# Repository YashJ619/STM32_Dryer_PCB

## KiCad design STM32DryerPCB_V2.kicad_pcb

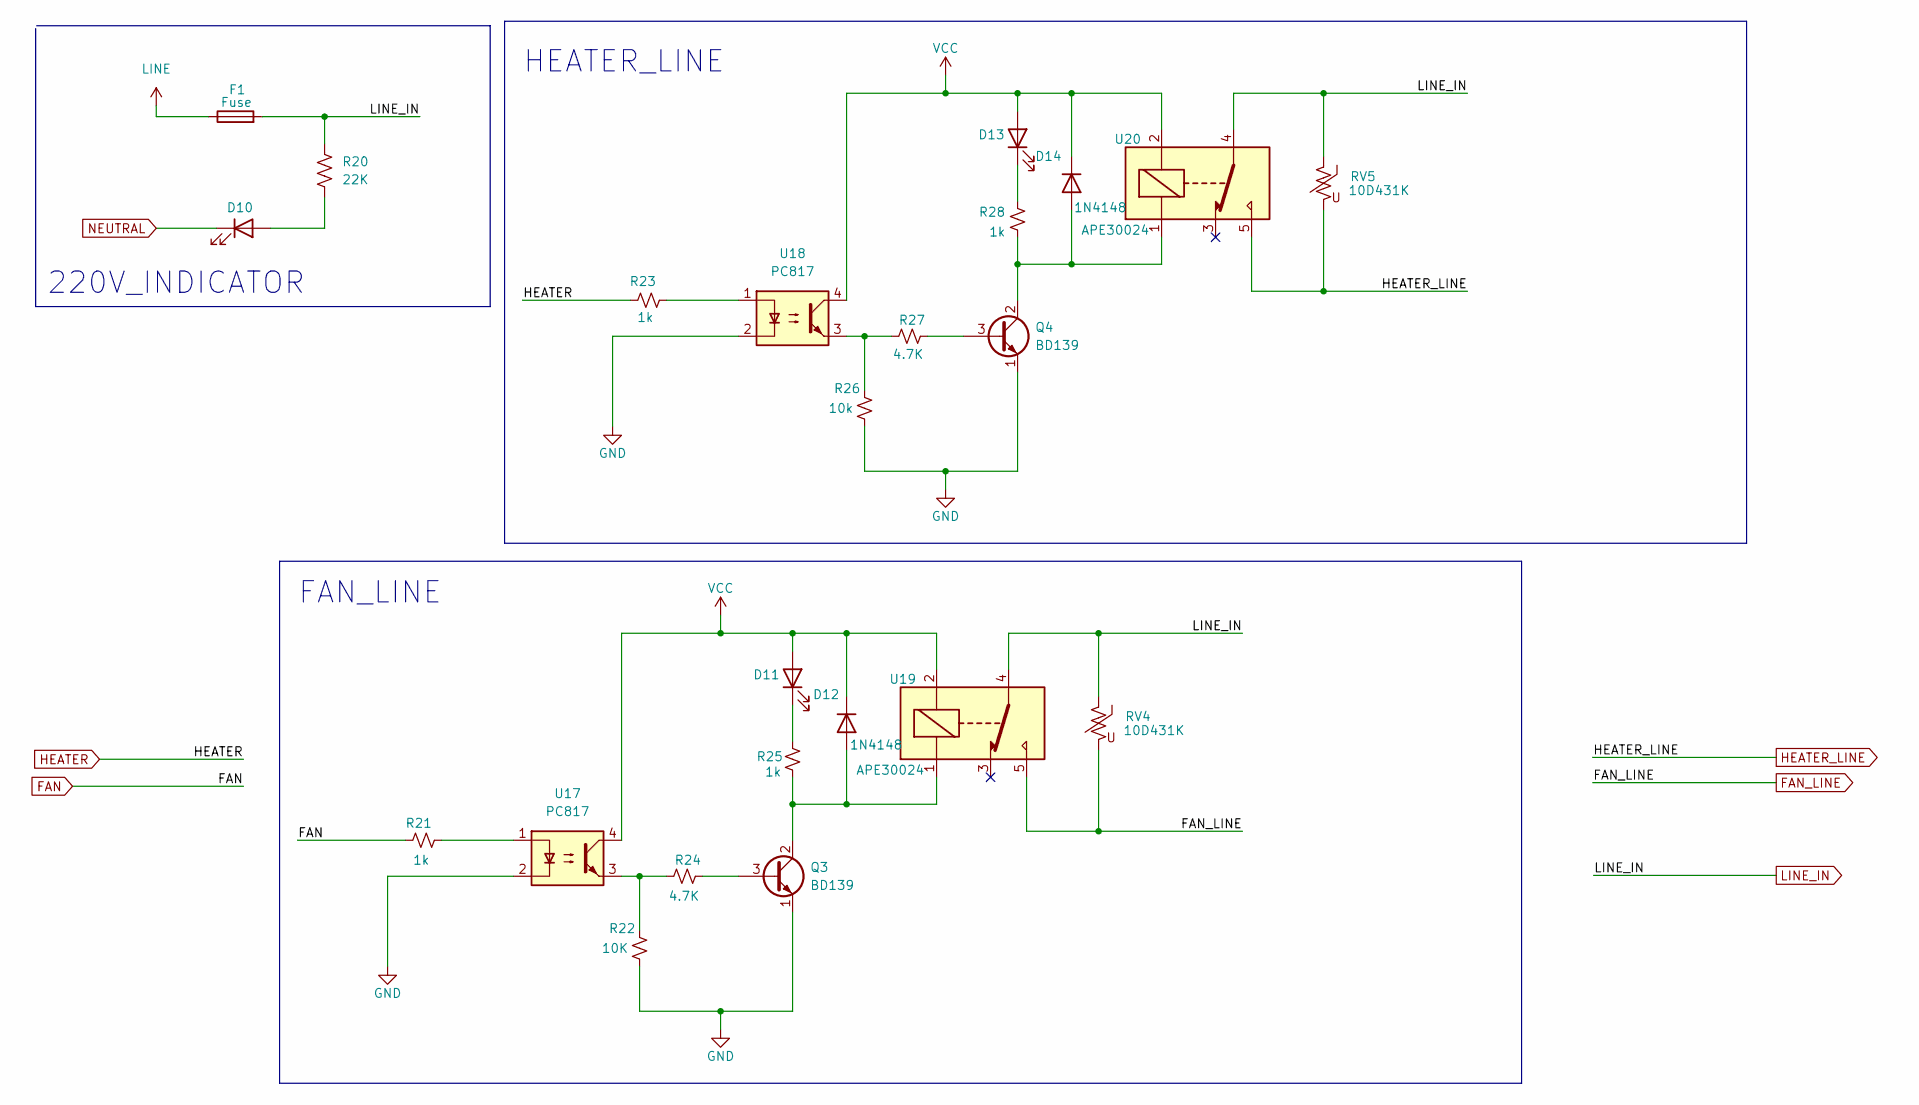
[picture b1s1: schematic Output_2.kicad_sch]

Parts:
D10, D11, D13: LED; LED_D3.0mm
D12, D14: 1N4148; D_DO-41_SOD81_P10.16mm_Horizontal
F1: Fuse; Fuseholder_Clip-5x20mm_Keystone_3518P_Inline_P23.11x6.76mm_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
Q3, Q4: BD139; TO-126-3_Vertical
R20: 22K; R_Axial_DIN0207_L6.3mm_D2.5mm_P10.16mm_Horizontal
R21, R23, R25, R28: 1k; R_Axial_DIN0207_L6.3mm_D2.5mm_P10.16mm_Horizontal
R22: 10K; R_Axial_DIN0207_L6.3mm_D2.5mm_P10.16mm_Horizontal
R24, R27: 4.7K; R_Axial_DIN0207_L6.3mm_D2.5mm_P10.16mm_Horizontal
R26: 10k; R_Axial_DIN0207_L6.3mm_D2.5mm_P10.16mm_Horizontal
RV4, RV5: 10D431K; RV_Disc_D7mm_W5.7mm_P5mm
U17, U18: PC817; DIP-4_W7.62mm_LongPads
U19, U20: APE30024; Relay_SPDT_28L_5W

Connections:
FAN: R21.1; also elsewhere on the board
FAN_LINE: RV4.2, U19.5; also elsewhere on the board
GND: Q3.1 (E), Q4.1 (E), R22.1, R26.1, U17.2, U18.2; also elsewhere on the board
HEATER: R23.1; also elsewhere on the board
HEATER_LINE: RV5.2, U20.5; also elsewhere on the board
LINE: F1.1; also elsewhere on the board
LINE_IN: F1.2, R20.1, RV4.1, RV5.1, U19.4, U20.4; also elsewhere on the board
NEUTRAL: D10.1 (K); also elsewhere on the board
unnamed: D10.2 (A), R20.2
unnamed: D11.1 (K), R25.2
unnamed: D12.2 (A), Q3.2 (C), R25.1, U19.1
unnamed: D13.1 (K), R28.2
unnamed: D14.2 (A), Q4.2 (C), R28.1, U20.1
unnamed: Q3.3 (B), R24.2
unnamed: Q4.3 (B), R27.2
unnamed: R21.2, U17.1
unnamed: R22.2, R24.1, U17.3
unnamed: R23.2, U18.1
unnamed: R26.2, R27.1, U18.3
VCC: D11.2 (A), D12.1 (K), D13.2 (A), D14.1 (K), U17.4, U18.4, U19.2, U20.2; also elsewhere on the board

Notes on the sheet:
HEATER_LINE
FAN_LINE
220V_INDICATOR

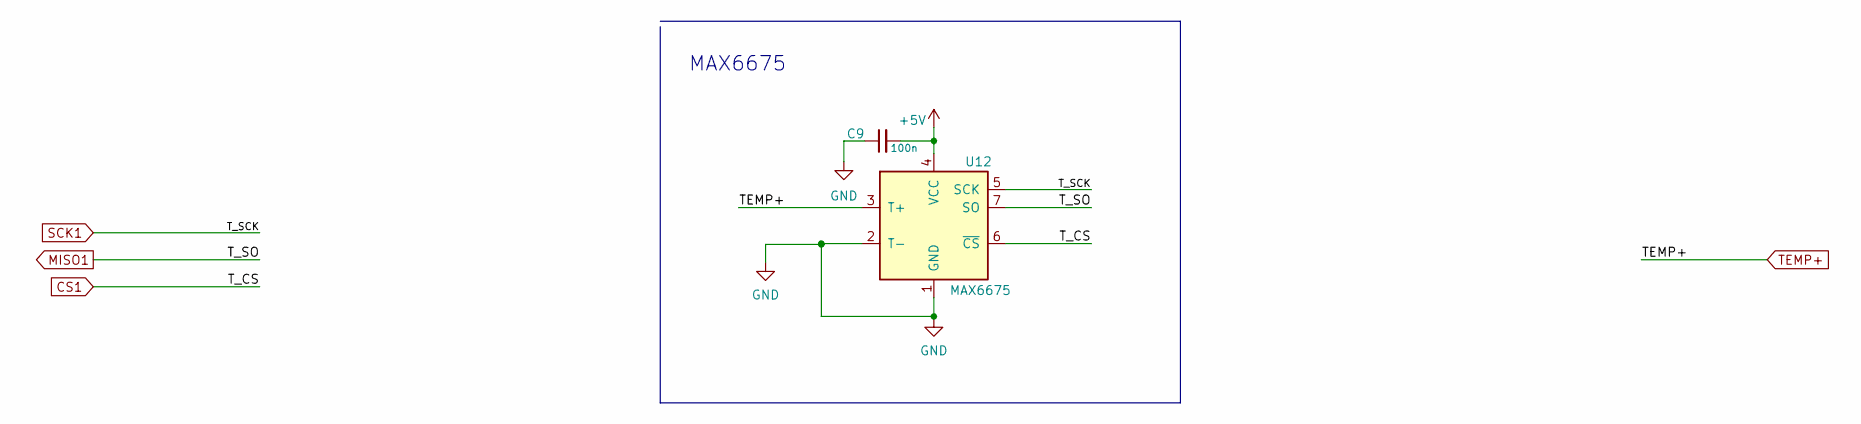
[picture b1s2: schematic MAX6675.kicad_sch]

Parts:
C9: 100n; C_Disc_D4.3mm_W1.9mm_P5.00mm
U12: MAX6675; SOIC-8_3.9x4.9mm_P1.27mm

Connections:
+5V: C9.2, U12.4 (VCC); also elsewhere on the board
CS1: U12.6 (~CS); also elsewhere on the board
GND: C9.1, U12.1 (GND), U12.2 (T-); also elsewhere on the board
MISO1: U12.7 (SO); also elsewhere on the board
SCK1: U12.5 (SCK); also elsewhere on the board
TEMP+: U12.3 (T+); also elsewhere on the board

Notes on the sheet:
MAX6675

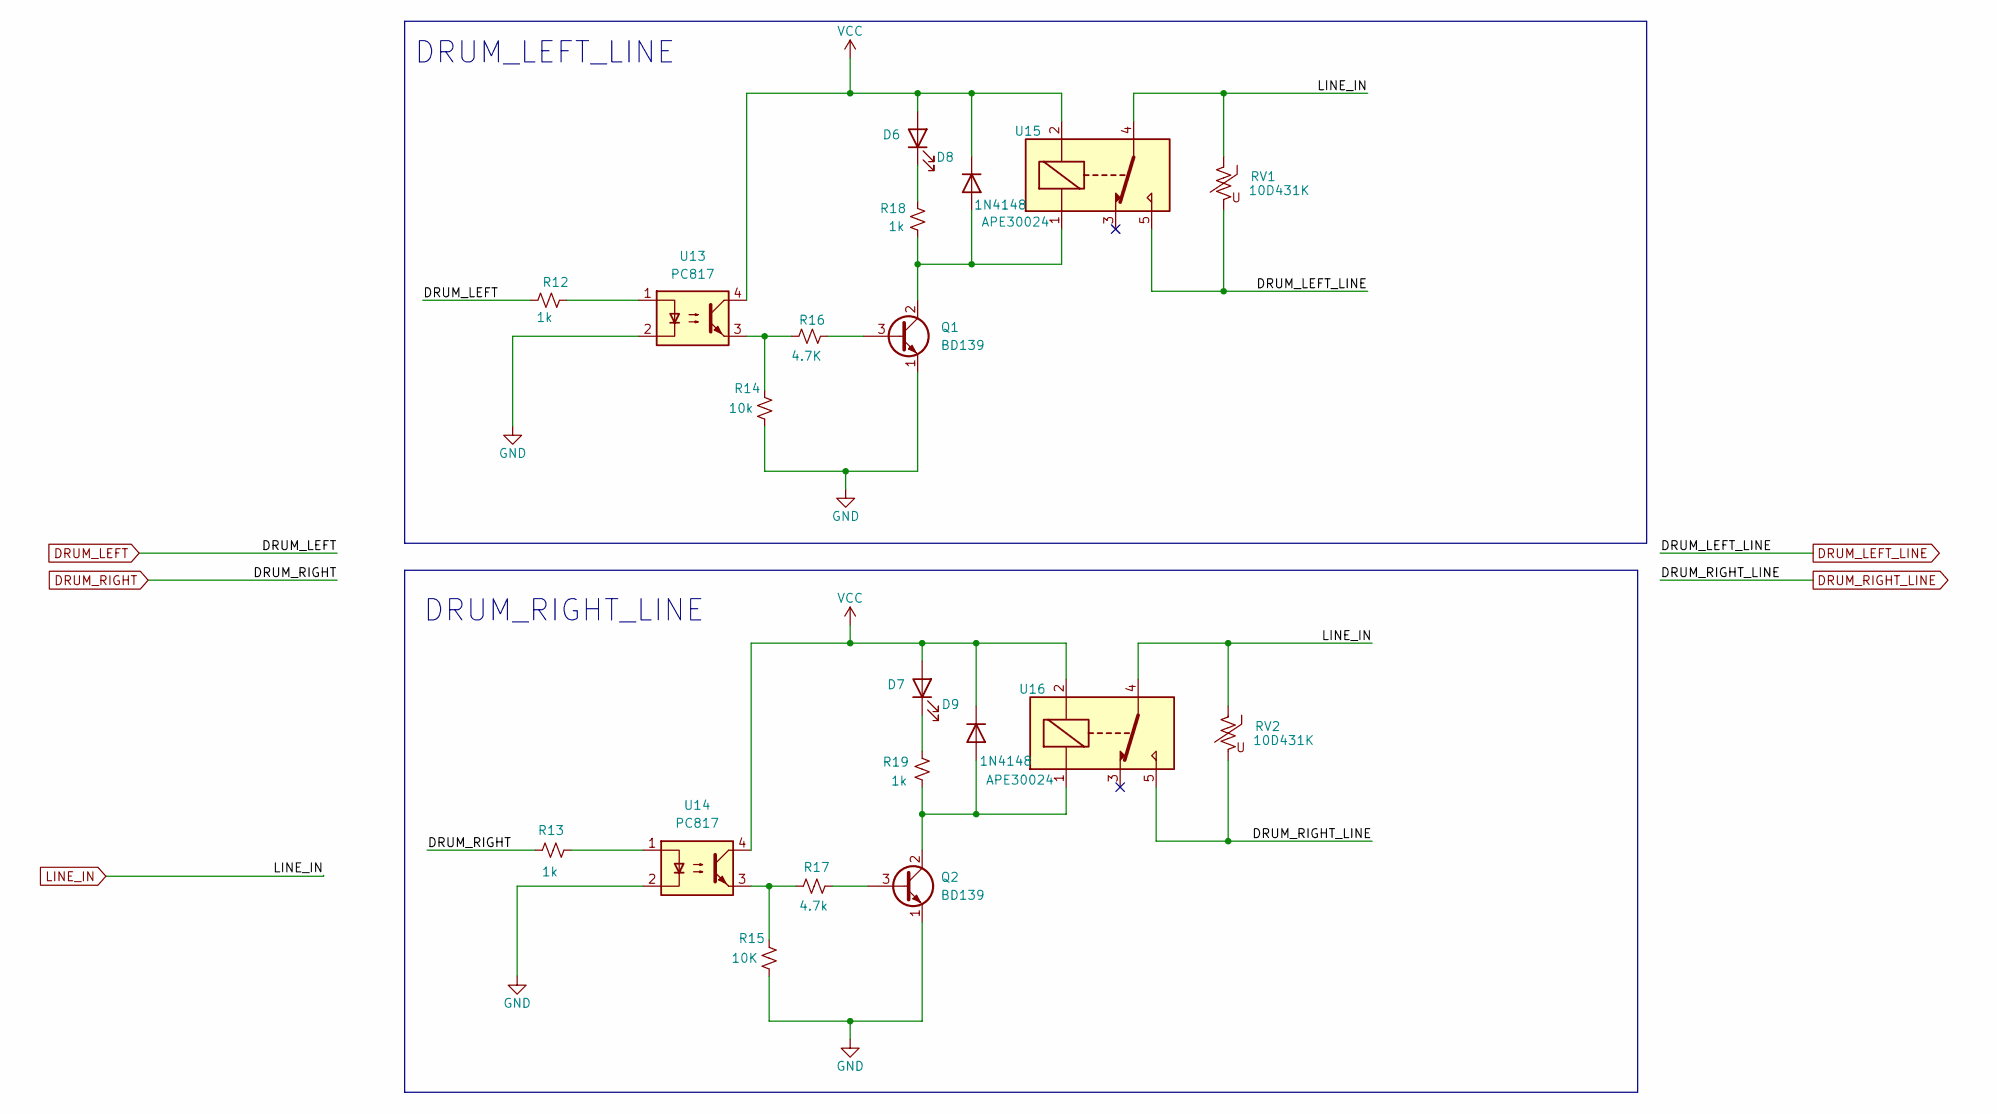
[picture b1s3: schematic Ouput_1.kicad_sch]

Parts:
D6, D7: LED; LED_D3.0mm
D8, D9: 1N4148; D_DO-41_SOD81_P10.16mm_Horizontal
Q1, Q2: BD139; TO-126-3_Vertical
R12, R13, R18, R19: 1k; R_Axial_DIN0207_L6.3mm_D2.5mm_P10.16mm_Horizontal
R14: 10k; R_Axial_DIN0207_L6.3mm_D2.5mm_P10.16mm_Horizontal
R15: 10K; R_Axial_DIN0207_L6.3mm_D2.5mm_P10.16mm_Horizontal
R16: 4.7K; R_Axial_DIN0207_L6.3mm_D2.5mm_P10.16mm_Horizontal
R17: 4.7k; R_Axial_DIN0207_L6.3mm_D2.5mm_P10.16mm_Horizontal
RV1, RV2: 10D431K; RV_Disc_D7mm_W5.7mm_P5mm
U13, U14: PC817; DIP-4_W7.62mm_LongPads
U15, U16: APE30024; Relay_SPDT_28L_5W

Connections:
DRUM_LEFT: R12.1; also elsewhere on the board
DRUM_LEFT_LINE: RV1.2, U15.5; also elsewhere on the board
DRUM_RIGHT: R13.1; also elsewhere on the board
DRUM_RIGHT_LINE: RV2.2, U16.5; also elsewhere on the board
GND: Q1.1 (E), Q2.1 (E), R14.1, R15.1, U13.2, U14.2; also elsewhere on the board
LINE_IN: RV1.1, RV2.1, U15.4, U16.4; also elsewhere on the board
unnamed: D6.1 (K), R18.2
unnamed: D7.1 (K), R19.2
unnamed: D8.2 (A), Q1.2 (C), R18.1, U15.1
unnamed: D9.2 (A), Q2.2 (C), R19.1, U16.1
unnamed: Q1.3 (B), R16.2
unnamed: Q2.3 (B), R17.2
unnamed: R12.2, U13.1
unnamed: R13.2, U14.1
unnamed: R14.2, R16.1, U13.3
unnamed: R15.2, R17.1, U14.3
VCC: D6.2 (A), D7.2 (A), D8.1 (K), D9.1 (K), U13.4, U14.4, U15.2, U16.2; also elsewhere on the board

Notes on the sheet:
DRUM_RIGHT_LINE
DRUM_LEFT_LINE

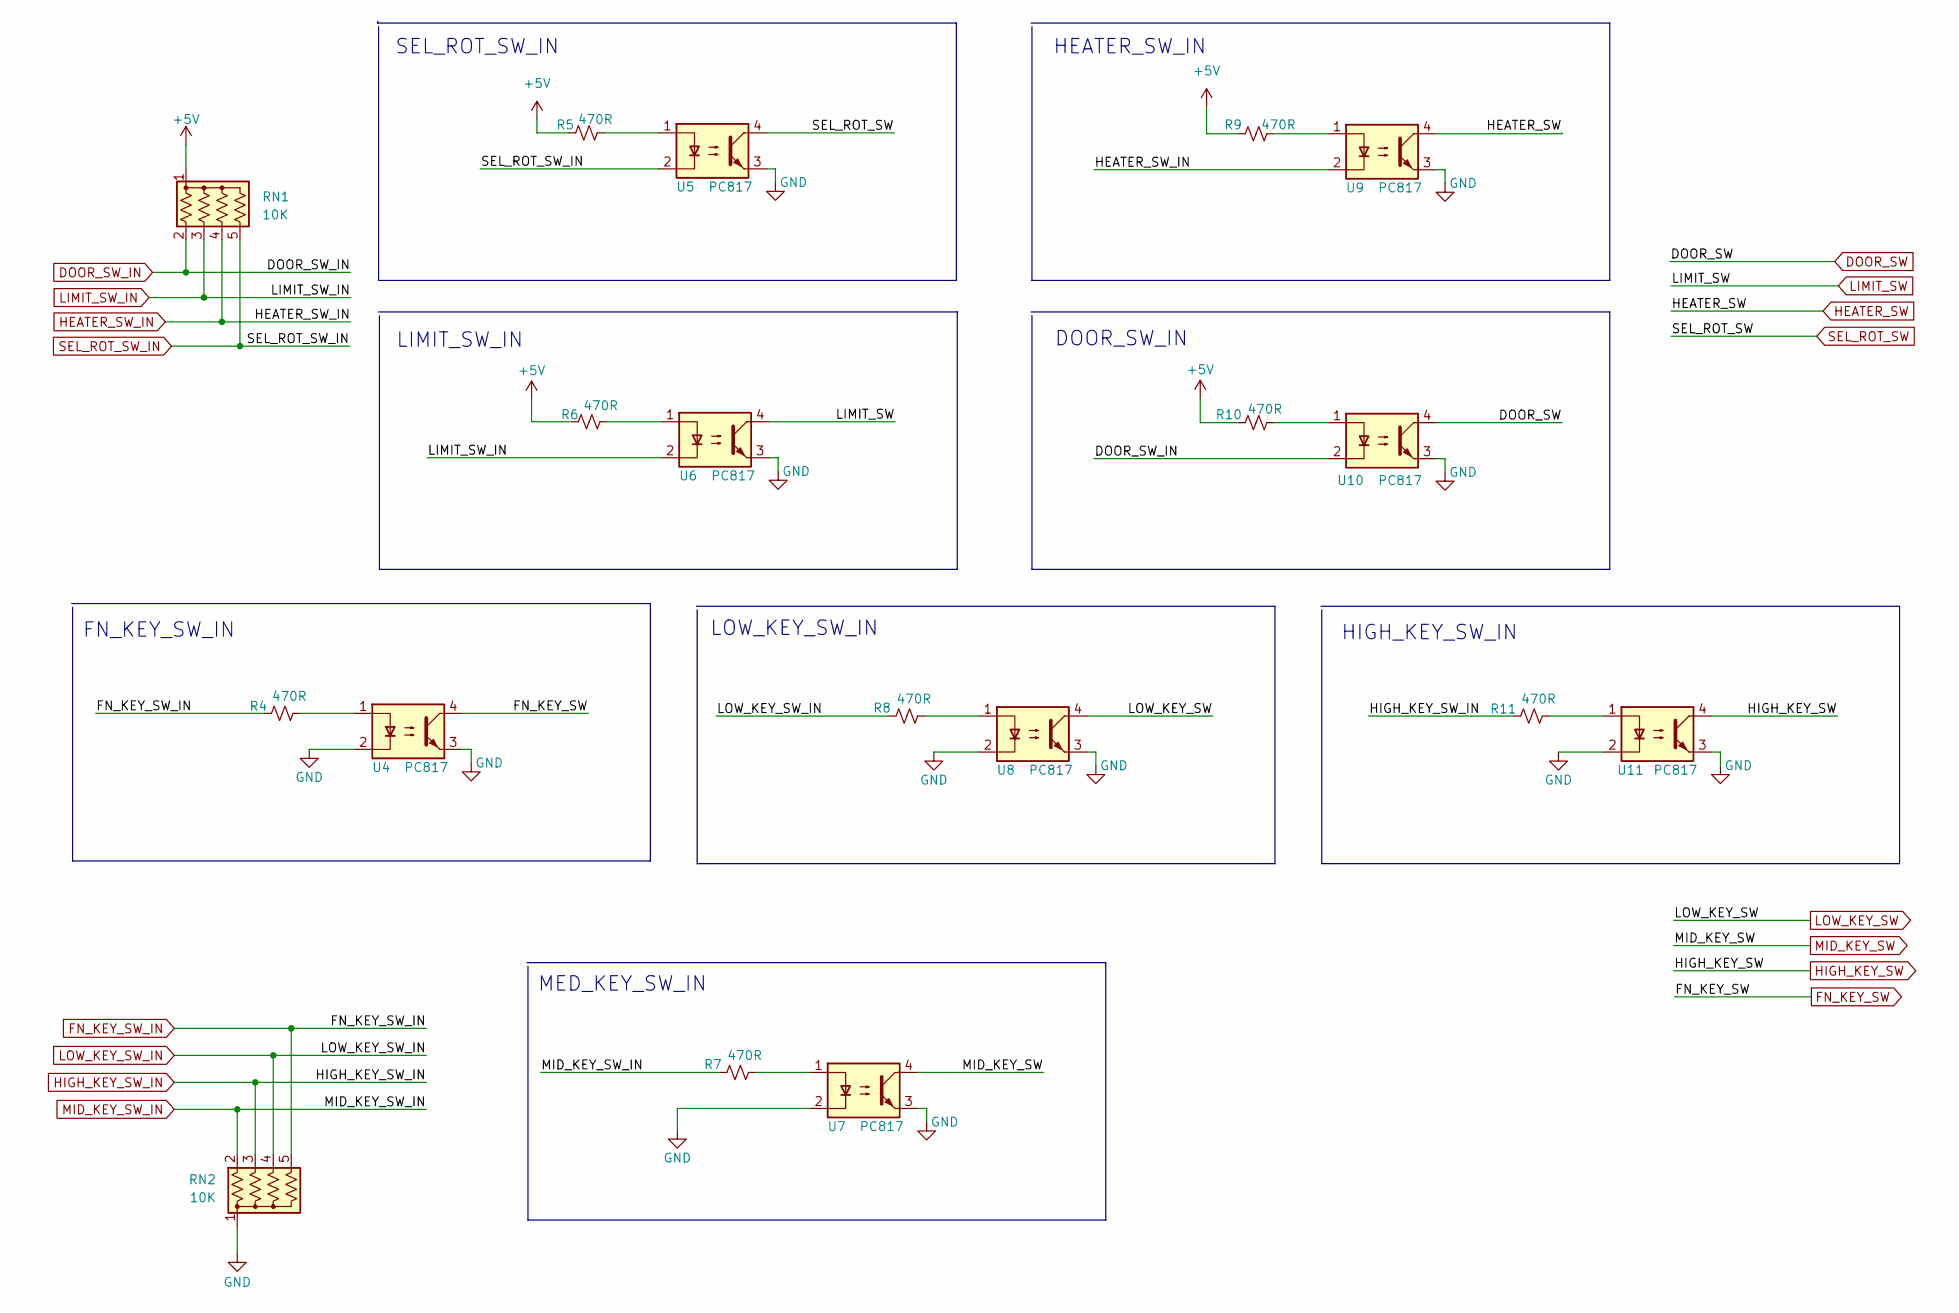
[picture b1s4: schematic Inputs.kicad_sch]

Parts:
R4, R5, R6, R7, R8, R9, R10, R11: 470R; R_Axial_DIN0207_L6.3mm_D2.5mm_P10.16mm_Horizontal
RN1, RN2: 10K; R_Array_SIP5
U4, U5, U6, U7, U8, U9, U10, U11: PC817; DIP-4_W7.62mm_LongPads

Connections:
+5V: R5.1, R6.1, R9.1, R10.1, RN1.1 (common); also elsewhere on the board
DOOR_SW: U10.4; also elsewhere on the board
DOOR_SW_IN: RN1.2 (R1), U10.2; also elsewhere on the board
FN_KEY_SW: U4.4; also elsewhere on the board
FN_KEY_SW_IN: R4.1, RN2.5 (R4); also elsewhere on the board
GND: RN2.1 (common), U4.2, U4.3, U5.3, U6.3, U7.2, U7.3, U8.2, U8.3, U9.3, U10.3, U11.2, U11.3; also elsewhere on the board
HEATER_SW: U9.4; also elsewhere on the board
HEATER_SW_IN: RN1.4 (R3), U9.2; also elsewhere on the board
HIGH_KEY_SW: U11.4; also elsewhere on the board
HIGH_KEY_SW_IN: R11.1, RN2.3 (R2); also elsewhere on the board
LIMIT_SW: U6.4; also elsewhere on the board
LIMIT_SW_IN: RN1.3 (R2), U6.2; also elsewhere on the board
LOW_KEY_SW: U8.4; also elsewhere on the board
LOW_KEY_SW_IN: R8.1, RN2.4 (R3); also elsewhere on the board
MID_KEY_SW: U7.4; also elsewhere on the board
MID_KEY_SW_IN: R7.1, RN2.2 (R1); also elsewhere on the board
unnamed: R4.2, U4.1
unnamed: R5.2, U5.1
unnamed: R6.2, U6.1
unnamed: R7.2, U7.1
unnamed: R8.2, U8.1
unnamed: R9.2, U9.1
unnamed: R10.2, U10.1
unnamed: R11.2, U11.1
SEL_ROT_SW: U5.4; also elsewhere on the board
SEL_ROT_SW_IN: RN1.5 (R4), U5.2; also elsewhere on the board

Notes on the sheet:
HEATER_SW_IN
LIMIT_SW_IN
LOW_KEY_SW_IN
HIGH_KEY_SW_IN
MED_KEY_SW_IN
FN_KEY_SW_IN
SEL_ROT_SW_IN
DOOR_SW_IN

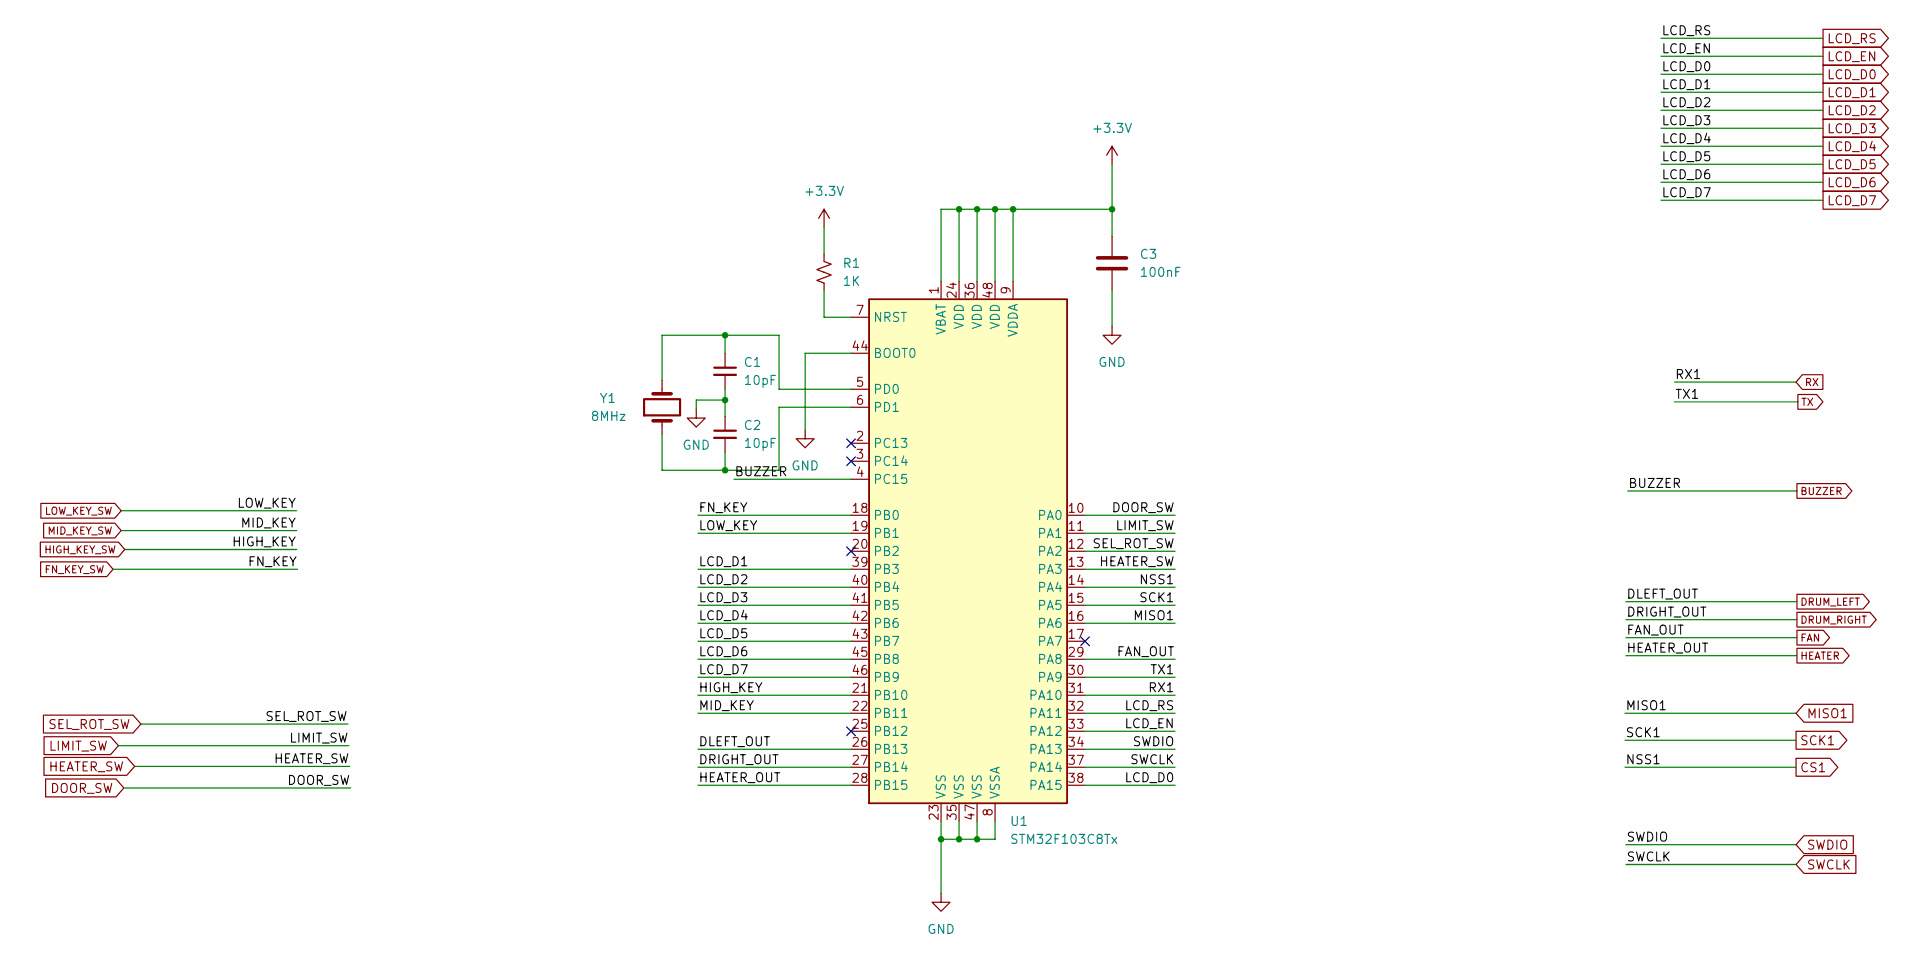
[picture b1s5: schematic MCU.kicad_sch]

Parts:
C1, C2: 10pF; C_Disc_D3.0mm_W1.6mm_P2.50mm
C3: 100nF; C_Disc_D4.3mm_W1.9mm_P5.00mm
R1: 1K; R_Axial_DIN0207_L6.3mm_D2.5mm_P10.16mm_Horizontal
U1: STM32F103C8Tx; LQFP-48_7x7mm_P0.5mm
Y1: 8MHz; Crystal_HC18-U_Vertical

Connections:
+3.3V: C3.1, R1.1, U1.1 (VBAT), U1.9 (VDDA), U1.24 (VDD), U1.36 (VDD), U1.48 (VDD); also elsewhere on the board
BUZZER: U1.4 (PC15); also elsewhere on the board
CS1: U1.14 (PA4); also elsewhere on the board
DOOR_SW: U1.10 (PA0); also elsewhere on the board
DRUM_LEFT: U1.26 (PB13); also elsewhere on the board
DRUM_RIGHT: U1.27 (PB14); also elsewhere on the board
FAN: U1.29 (PA8); also elsewhere on the board
FN_KEY_SW: U1.18 (PB0); also elsewhere on the board
GND: C1.2, C2.1, C3.2, U1.8 (VSSA), U1.23 (VSS), U1.35 (VSS), U1.44 (BOOT0), U1.47 (VSS); also elsewhere on the board
HEATER: U1.28 (PB15); also elsewhere on the board
HEATER_SW: U1.13 (PA3); also elsewhere on the board
HIGH_KEY_SW: U1.21 (PB10); also elsewhere on the board
LCD_D0: U1.38 (PA15); also elsewhere on the board
LCD_D1: U1.39 (PB3); also elsewhere on the board
LCD_D2: U1.40 (PB4); also elsewhere on the board
LCD_D3: U1.41 (PB5); also elsewhere on the board
LCD_D4: U1.42 (PB6); also elsewhere on the board
LCD_D5: U1.43 (PB7); also elsewhere on the board
LCD_D6: U1.45 (PB8); also elsewhere on the board
LCD_D7: U1.46 (PB9); also elsewhere on the board
LCD_EN: U1.33 (PA12); also elsewhere on the board
LCD_RS: U1.32 (PA11); also elsewhere on the board
LIMIT_SW: U1.11 (PA1); also elsewhere on the board
LOW_KEY_SW: U1.19 (PB1); also elsewhere on the board
MID_KEY_SW: U1.22 (PB11); also elsewhere on the board
MISO1: U1.16 (PA6); also elsewhere on the board
unnamed: C1.1, U1.5 (PD0), Y1.2
unnamed: C2.2, U1.6 (PD1), Y1.1
unnamed: R1.2, U1.7 (NRST)
RX: U1.31 (PA10)
SCK1: U1.15 (PA5); also elsewhere on the board
SEL_ROT_SW: U1.12 (PA2); also elsewhere on the board
SWCLK: U1.37 (PA14); also elsewhere on the board
SWDIO: U1.34 (PA13); also elsewhere on the board
TX: U1.30 (PA9)

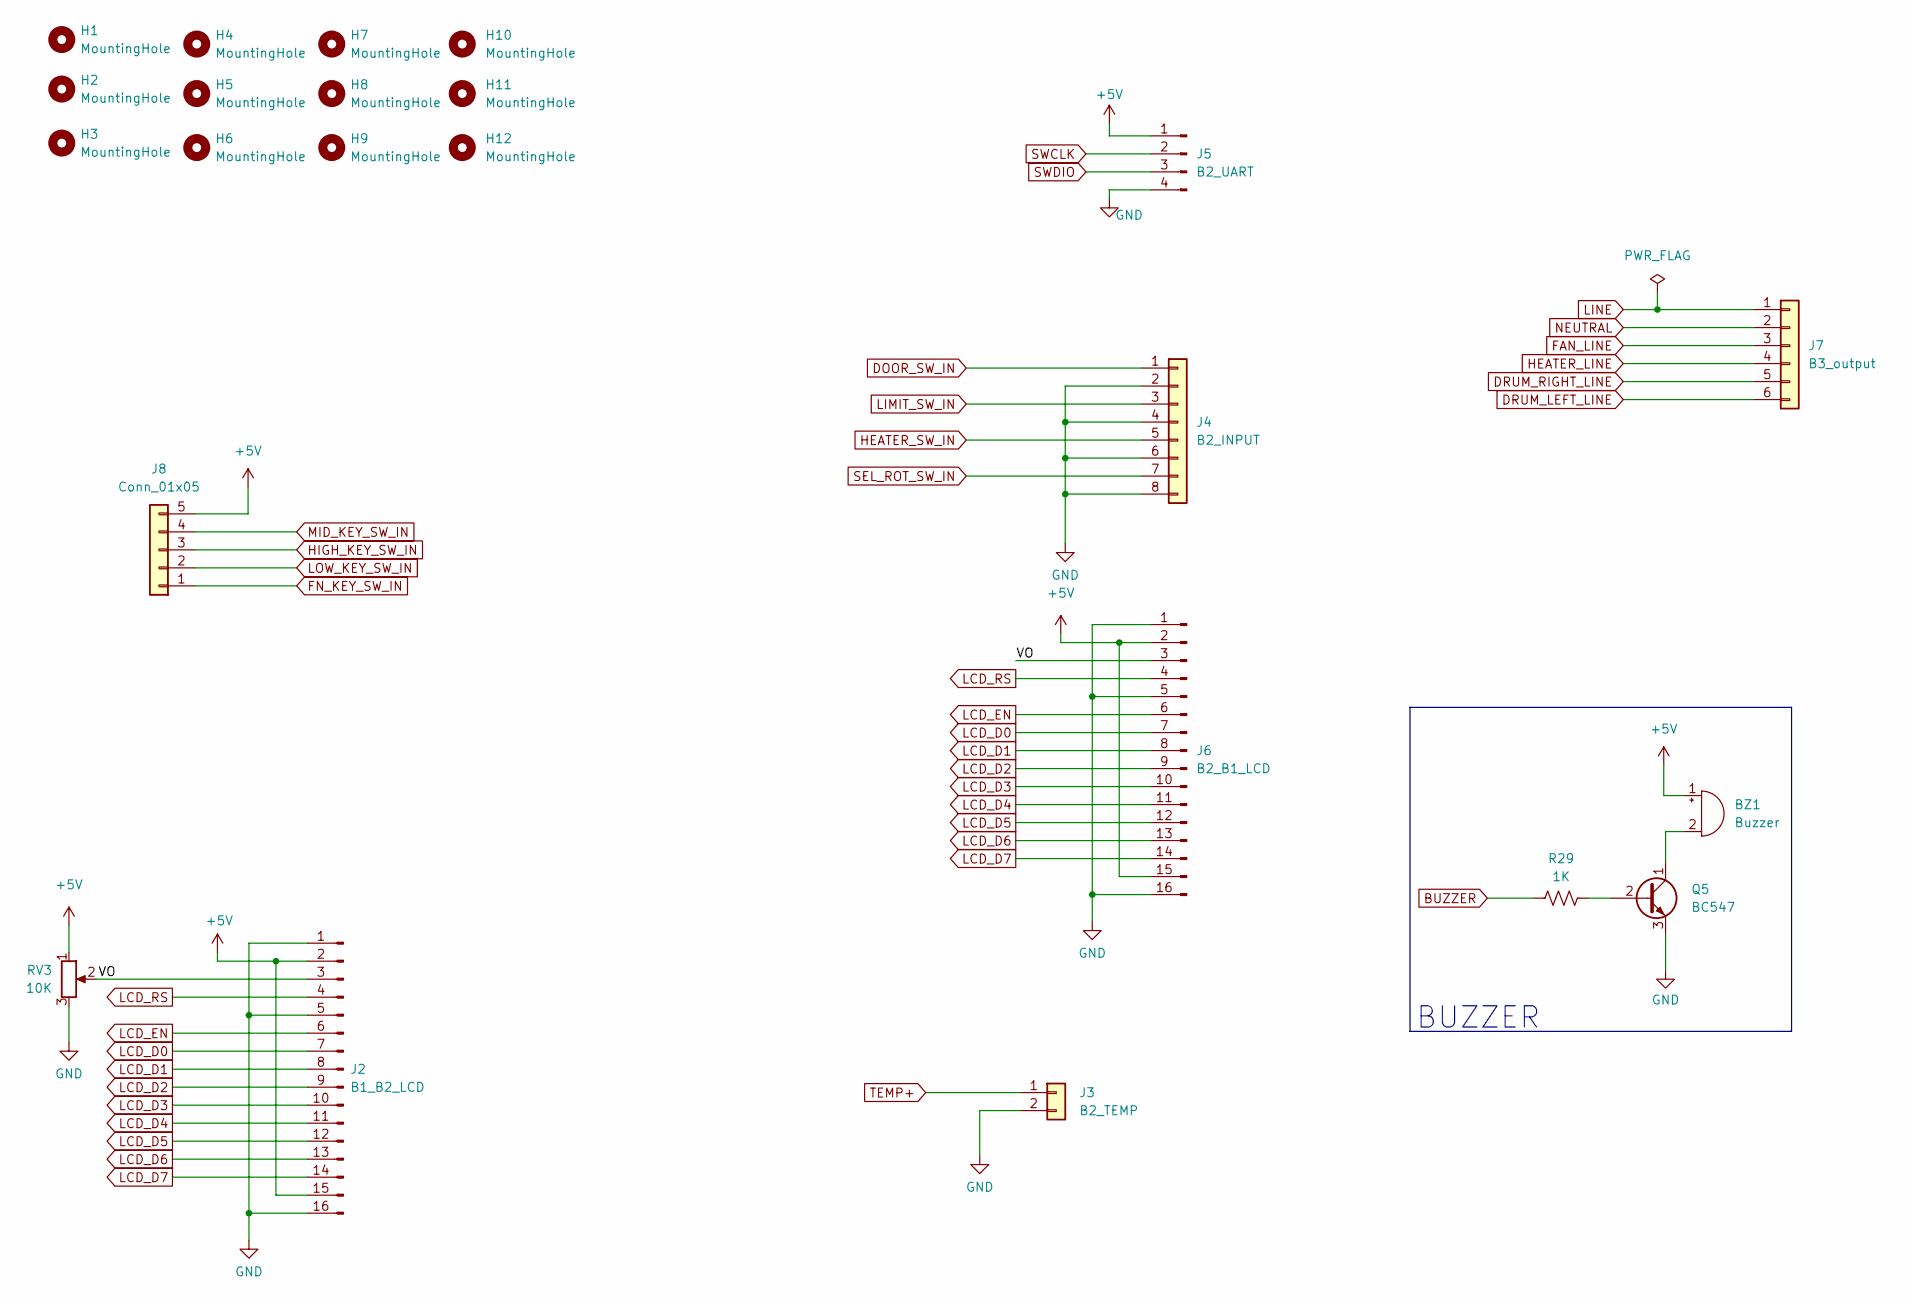
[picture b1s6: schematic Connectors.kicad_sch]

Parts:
BZ1: Buzzer; Buzzer_12x9.5RM7.6
H1, H2, H3, H4, H5, H6, H7, H8, H9, H10, H11, H12: MountingHole; MountingHole_3mm_Pad
J2: B1_B2_LCD; PinHeader_1x16_P2.54mm_Vertical
J3: B2_TEMP; PhoenixContact_MCV_1,5_2-G-5.08_1x02_P5.08mm_Vertical
J4: B2_INPUT; Stocko_MKS_1658-6-0-808_1x8_P2.50mm_Vertical
J5: B2_UART; PinHeader_1x04_P2.54mm_Vertical
J6: B2_B1_LCD; PinHeader_1x16_P2.54mm_Vertical
J7: B3_output; PhoenixContact_MCV_1,5_6-G-5.08_1x06_P5.08mm_Vertical
J8: Conn_01x05; PinHeader_1x05_P2.54mm_Vertical
Q5: BC547; TO-92_Inline
R29: 1K; R_Axial_DIN0207_L6.3mm_D2.5mm_P10.16mm_Horizontal
RV3: 10K; Potentiometer_Bourns_3266W_Vertical

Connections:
+5V: BZ1.1 (-), J2.2, J2.15, J5.1, J6.2, J6.15, J8.5, RV3.1; also elsewhere on the board
/Connectors/VO: J2.3, J6.3, RV3.2
BUZZER: R29.1; also elsewhere on the board
DOOR_SW_IN: J4.1; also elsewhere on the board
DRUM_LEFT_LINE: J7.6; also elsewhere on the board
DRUM_RIGHT_LINE: J7.5; also elsewhere on the board
FAN_LINE: J7.3; also elsewhere on the board
FN_KEY_SW_IN: J8.1; also elsewhere on the board
GND: J2.1, J2.5, J2.16, J3.2, J4.2, J4.4, J4.6, J4.8, J5.4, J6.1, J6.5, J6.16, Q5.3 (E), RV3.3; also elsewhere on the board
HEATER_LINE: J7.4; also elsewhere on the board
HEATER_SW_IN: J4.5; also elsewhere on the board
HIGH_KEY_SW_IN: J8.3; also elsewhere on the board
LCD_D0: J2.7, J6.7; also elsewhere on the board
LCD_D1: J2.8, J6.8; also elsewhere on the board
LCD_D2: J2.9, J6.9; also elsewhere on the board
LCD_D3: J2.10, J6.10; also elsewhere on the board
LCD_D4: J2.11, J6.11; also elsewhere on the board
LCD_D5: J2.12, J6.12; also elsewhere on the board
LCD_D6: J2.13, J6.13; also elsewhere on the board
LCD_D7: J2.14, J6.14; also elsewhere on the board
LCD_EN: J2.6, J6.6; also elsewhere on the board
LCD_RS: J2.4, J6.4; also elsewhere on the board
LIMIT_SW_IN: J4.3; also elsewhere on the board
LINE: J7.1; also elsewhere on the board
LOW_KEY_SW_IN: J8.2; also elsewhere on the board
MID_KEY_SW_IN: J8.4; also elsewhere on the board
NEUTRAL: J7.2; also elsewhere on the board
unnamed: BZ1.2 (+), Q5.1 (C)
unnamed: Q5.2 (B), R29.2
SEL_ROT_SW_IN: J4.7; also elsewhere on the board
SWCLK: J5.2; also elsewhere on the board
SWDIO: J5.3; also elsewhere on the board
TEMP+: J3.1; also elsewhere on the board

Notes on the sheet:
BUZZER

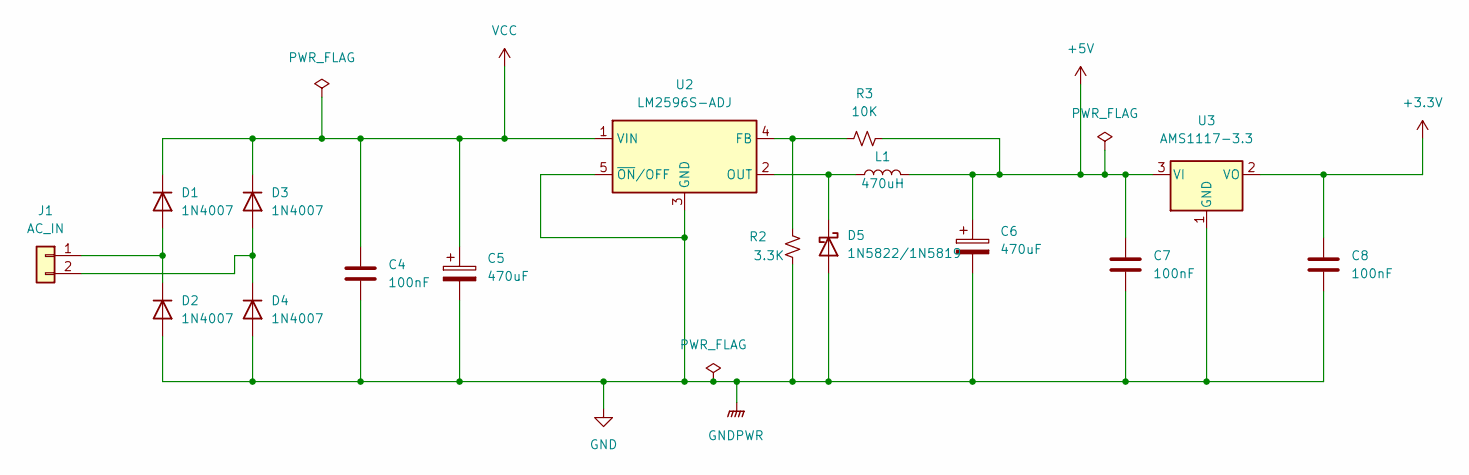
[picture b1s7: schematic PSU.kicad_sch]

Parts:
C4, C7, C8: 100nF; C_Disc_D4.3mm_W1.9mm_P5.00mm
C5, C6: 470uF; CP_Radial_D8.0mm_P2.50mm
D1, D2, D3, D4: 1N4007; D_DO-41_SOD81_P10.16mm_Horizontal
D5: 1N5822/1N5819; D_DO-41_SOD81_P10.16mm_Horizontal
J1: AC_IN; PhoenixContact_MCV_1,5_2-G-5.08_1x02_P5.08mm_Vertical
L1: 470uH; L_12x12mm_H8mm
R2: 3.3K; R_Axial_DIN0207_L6.3mm_D2.5mm_P10.16mm_Horizontal
R3: 10K; R_Axial_DIN0207_L6.3mm_D2.5mm_P10.16mm_Horizontal
U2: LM2596S-ADJ; TO-263-5_TabPin3
U3: AMS1117-3.3; SOT-223-3_TabPin2

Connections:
+3.3V: C8.1, U3.2 (VO); also elsewhere on the board
+5V: C6.1, C7.1, L1.2, R3.2, U3.3 (VI); also elsewhere on the board
GND: C4.2, C5.2, C6.2, C7.2, C8.2, D2.2 (A), D4.2 (A), D5.2 (A), R2.1, U2.3 (GND), U2.5 (~ON/OFF), U3.1 (GND); also elsewhere on the board
unnamed: D1.2 (A), D2.1 (K), J1.1
unnamed: D3.2 (A), D4.1 (K), J1.2
unnamed: D5.1 (K), L1.1, U2.2 (OUT)
unnamed: R2.2, R3.1, U2.4 (FB)
VCC: C4.1, C5.1, D1.1 (K), D3.1 (K), U2.1 (VIN); also elsewhere on the board

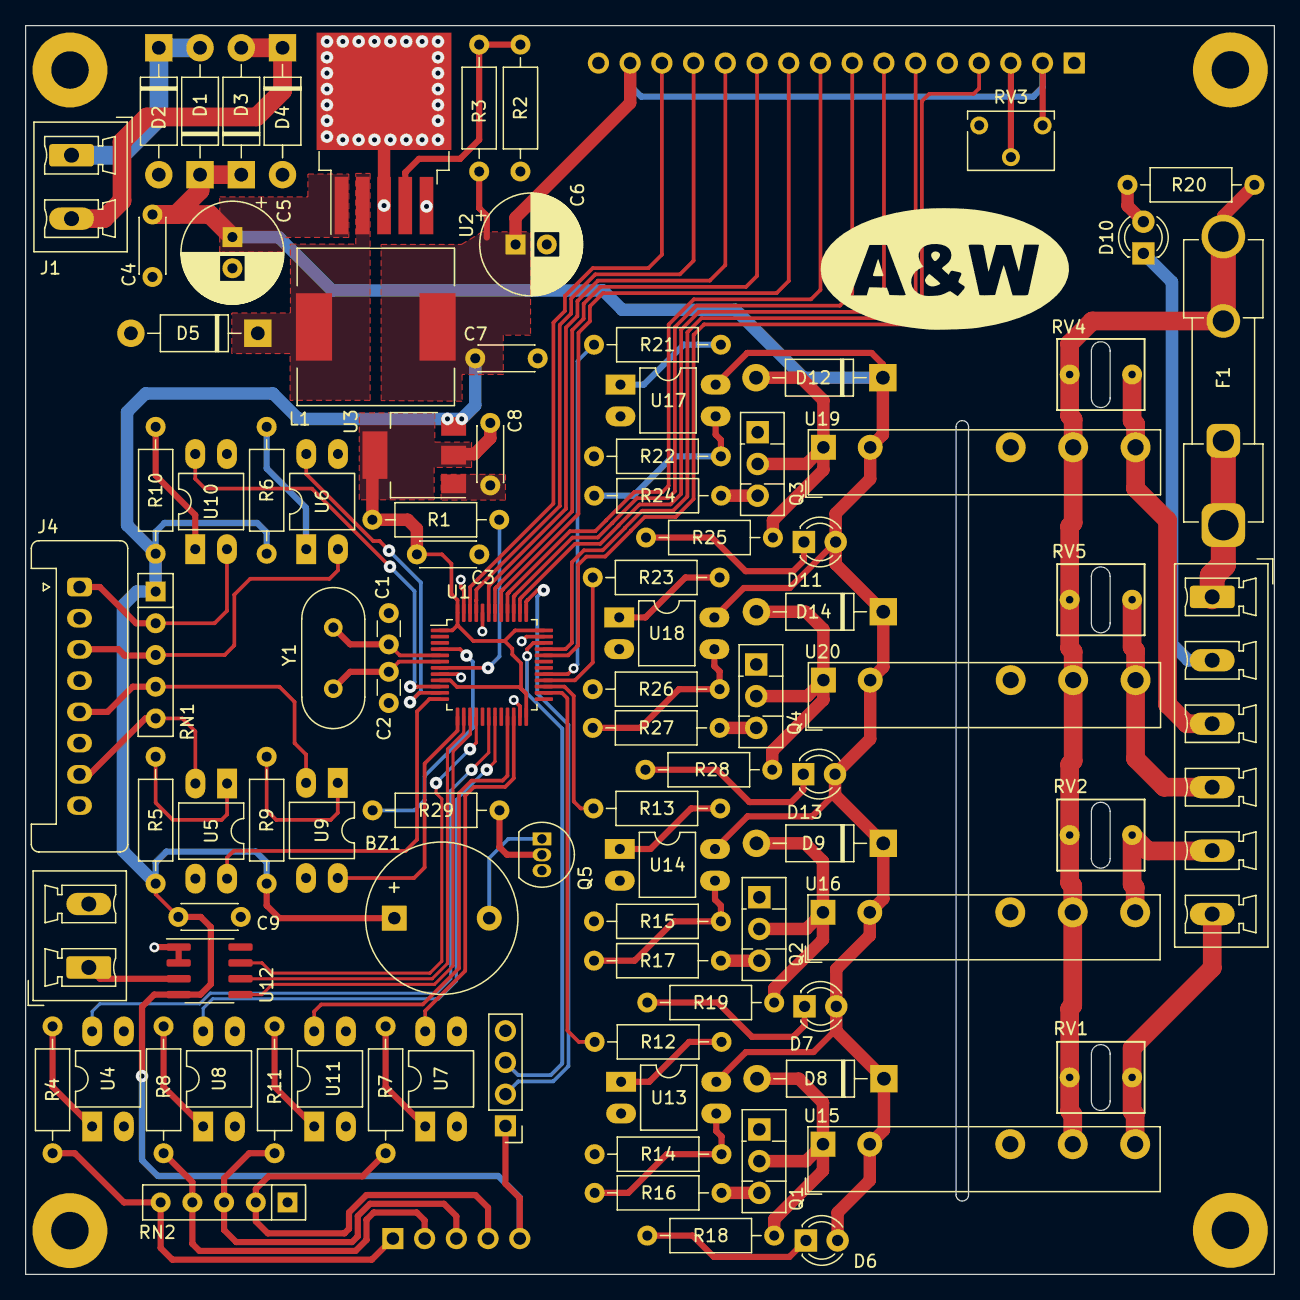
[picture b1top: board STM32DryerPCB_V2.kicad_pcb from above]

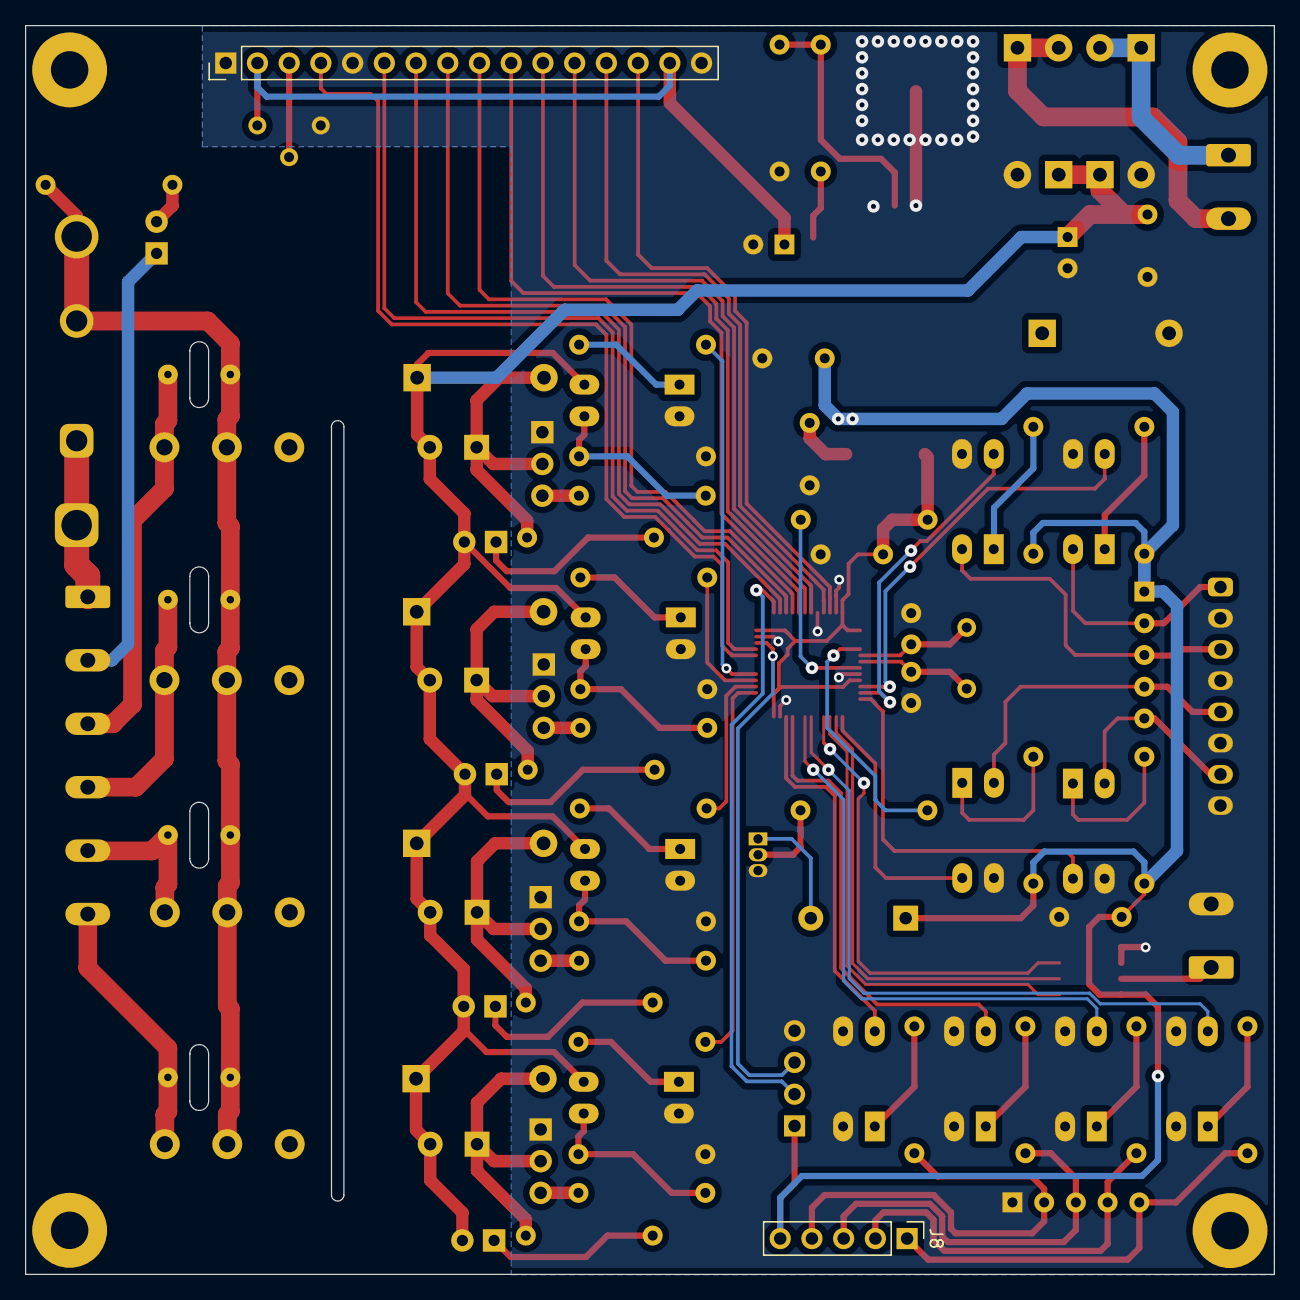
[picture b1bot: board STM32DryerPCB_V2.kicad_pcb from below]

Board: 2 copper layers, 100.0 x 100.0 mm, 99 parts (2 on the bottom side), 87 nets.
